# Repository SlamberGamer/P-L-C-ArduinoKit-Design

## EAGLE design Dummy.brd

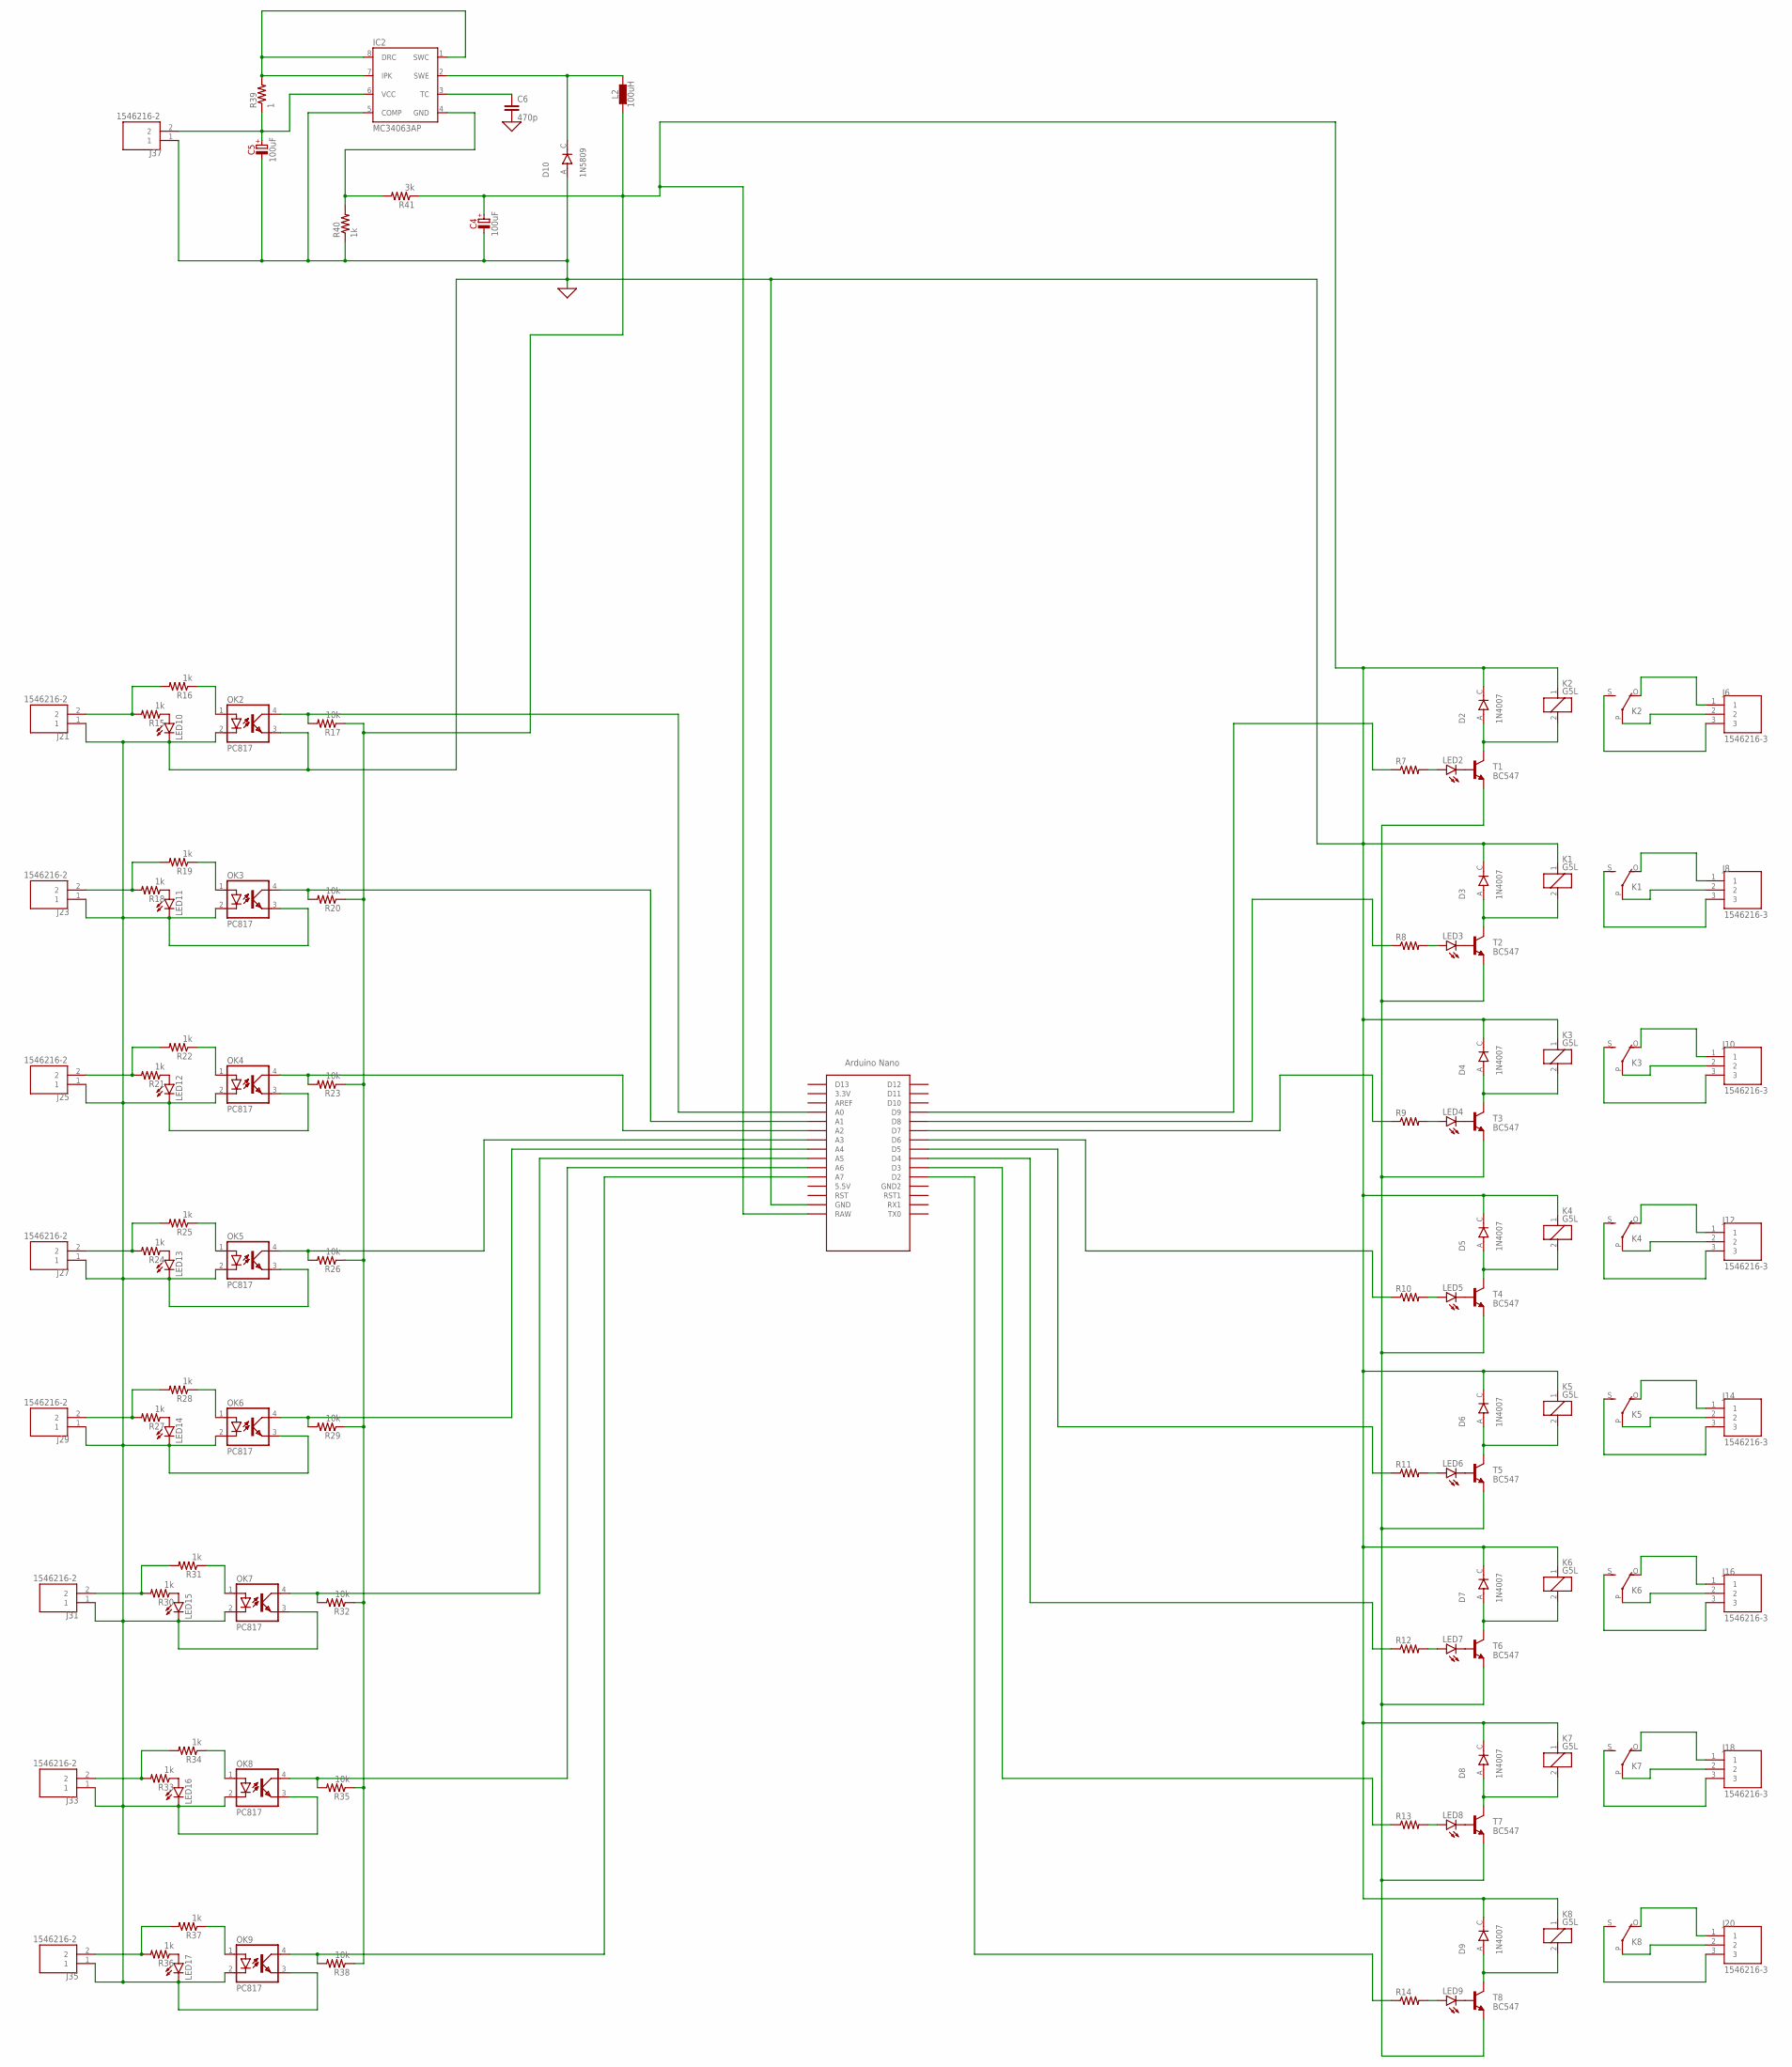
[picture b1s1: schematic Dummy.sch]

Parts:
C4, C5: 100uF; E1,5-4
C6: 470p; C2.5-2
D2, D3, D4, D5, D6, D7, D8, D9: 1N4007; DIOAD1060W80L520D270
D10: 1N5809; DIOAD1060W80L520D270
IC2: MC34063AP; DIL-08
J6, J8, J10, J12, J14, J16, J18, J20: 1546216-3; TE_1546216-3
J21, J23, J25, J27, J29, J31, J33, J35, J37: 1546216-2; TE_1546216-2
K1, K2, K3, K4, K5, K6, K7, K8: G5L; G5LE
L2: 100uH; L_NR80XX
LED2, LED3, LED4, LED5, LED6, LED7, LED8, LED9, LED10, LED11, LED12, LED13, LED14, LED15, LED16, LED17: LED3MM
OK2, OK3, OK4, OK5, OK6, OK7, OK8, OK9: PC817; DIL04
R7, R8, R9, R10, R11, R12, R13, R14: R-US_0207/15; 0207/15
R15, R16, R18, R19, R21, R22, R24, R25, R27, R28, R30, R31, R33, R34, R36, R37: 1k; 0207/15
R17, R20, R23, R26, R29, R32, R35, R38: 10k; 0207/15
R39: 1; 0207/12
R40: 1k; 0207/12
R41: 3k; 0207/12
T1, T2, T3, T4, T5, T6, T7, T8: BC547; TO92
U$1: NANO

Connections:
0: C4.+, C4.-, C5.-, C6.2, D2.C, D3.C, D4.C, D5.C, D6.C, D7.C, D8.C, D9.C, D10.A, IC2.5 (COMP), J21.1, J23.1, J25.1, J27.1, J29.1, J31.1, J33.1, J35.1, J37.1, K1.1, K2.1, K3.1, K4.1, K5.1, K6.1, K7.1, K8.1, L2.1, LED10.K (C), LED11.K (C), LED12.K (C), LED13.K (C), LED14.K (C), LED15.K (C), LED16.K (C), LED17.K (C), OK2.2 (C), OK2.3 (EMIT), OK3.2 (C), OK3.3 (EMIT), OK4.2 (C), OK4.3 (EMIT), OK5.2 (C), OK5.3 (EMIT), OK6.2 (C), OK6.3 (EMIT), OK7.2 (C), OK7.3 (EMIT), OK8.2 (C), OK8.3 (EMIT), OK9.2 (C), OK9.3 (EMIT), R17.1, R20.1, R23.1, R26.1, R29.1, R32.1, R35.1, R38.1, R40.1, R41.1, U$1.GND, U$1.RAW
unnamed: LED2.K (C), T1.2 (B)
unnamed: R7.1, U$1.D9
unnamed: LED2.A, R7.2
unnamed: D2.A, K2.2, T1.3 (C)
unnamed: J6.1, K2.O
unnamed: J6.2, K2.P
unnamed: J6.3, K2.S
unnamed: LED3.K (C), T2.2 (B)
unnamed: R8.1, U$1.D8
unnamed: LED3.A, R8.2
unnamed: D3.A, K1.2, T2.3 (C)
unnamed: J8.1, K1.O
unnamed: J8.2, K1.P
unnamed: J8.3, K1.S
unnamed: LED4.K (C), T3.2 (B)
unnamed: R9.1, U$1.D7
unnamed: LED4.A, R9.2
unnamed: D4.A, K3.2, T3.3 (C)
unnamed: J10.1, K3.O
unnamed: J10.2, K3.P
unnamed: J10.3, K3.S
unnamed: LED5.K (C), T4.2 (B)
unnamed: R10.1, U$1.D6
unnamed: LED5.A, R10.2
unnamed: D5.A, K4.2, T4.3 (C)
unnamed: J12.1, K4.O
unnamed: J12.2, K4.P
unnamed: J12.3, K4.S
unnamed: LED6.K (C), T5.2 (B)
unnamed: R11.1, U$1.D5
unnamed: LED6.A, R11.2
unnamed: D6.A, K5.2, T5.3 (C)
unnamed: J14.1, K5.O
unnamed: J14.2, K5.P
unnamed: J14.3, K5.S
unnamed: LED7.K (C), T6.2 (B)
unnamed: R12.1, U$1.D4
unnamed: LED7.A, R12.2
unnamed: D7.A, K6.2, T6.3 (C)
unnamed: J16.1, K6.O
unnamed: J16.2, K6.P
unnamed: J16.3, K6.S
unnamed: LED8.K (C), T7.2 (B)
unnamed: R13.1, U$1.D3
unnamed: LED8.A, R13.2
unnamed: D8.A, K7.2, T7.3 (C)
unnamed: J18.1, K7.O
unnamed: J18.2, K7.P
unnamed: J18.3, K7.S
unnamed: LED9.K (C), T8.2 (B)
unnamed: R14.1, U$1.D2
unnamed: LED9.A, R14.2
unnamed: D9.A, K8.2, T8.3 (C)
unnamed: T1.1 (E), T2.1 (E), T3.1 (E), T4.1 (E), T5.1 (E), T6.1 (E), T7.1 (E), T8.1 (E)
unnamed: J20.1, K8.O
unnamed: J20.2, K8.P
unnamed: J20.3, K8.S
unnamed: LED10.A, R15.1
unnamed: J21.2, R15.2, R16.2
unnamed: OK2.1 (A), R16.1
unnamed: OK2.4 (COL), R17.2, U$1.A0
unnamed: LED11.A, R18.1
unnamed: J23.2, R18.2, R19.2
unnamed: OK3.1 (A), R19.1
unnamed: OK3.4 (COL), R20.2, U$1.A1
unnamed: LED12.A, R21.1
unnamed: J25.2, R21.2, R22.2
unnamed: OK4.1 (A), R22.1
unnamed: OK4.4 (COL), R23.2, U$1.A2
unnamed: LED13.A, R24.1
unnamed: J27.2, R24.2, R25.2
unnamed: OK5.1 (A), R25.1
unnamed: OK5.4 (COL), R26.2, U$1.A3
unnamed: LED14.A, R27.1
unnamed: J29.2, R27.2, R28.2
unnamed: OK6.1 (A), R28.1
unnamed: OK6.4 (COL), R29.2, U$1.A4
unnamed: LED15.A, R30.1
unnamed: J31.2, R30.2, R31.2
unnamed: OK7.1 (A), R31.1
unnamed: OK7.4 (COL), R32.2, U$1.A5
unnamed: LED16.A, R33.1
unnamed: J33.2, R33.2, R34.2
unnamed: OK8.1 (A), R34.1
unnamed: OK8.4 (COL), R35.2, U$1.A6
unnamed: LED17.A, R36.1
unnamed: J35.2, R36.2, R37.2
unnamed: OK9.1 (A), R37.1
unnamed: OK9.4 (COL), R38.2, U$1.A7
unnamed: IC2.1 (SWC), IC2.7 (IPK), IC2.8 (DRC), R39.2
unnamed: D10.C, IC2.2 (SWE), L2.2
unnamed: C6.1, IC2.3 (TC)
unnamed: IC2.4 (GND), R40.2, R41.2
unnamed: C5.+, IC2.6 (VCC), J37.2, R39.1

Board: 2 copper layers, 107 parts (0 on the bottom side), 95 nets, no tracks yet.

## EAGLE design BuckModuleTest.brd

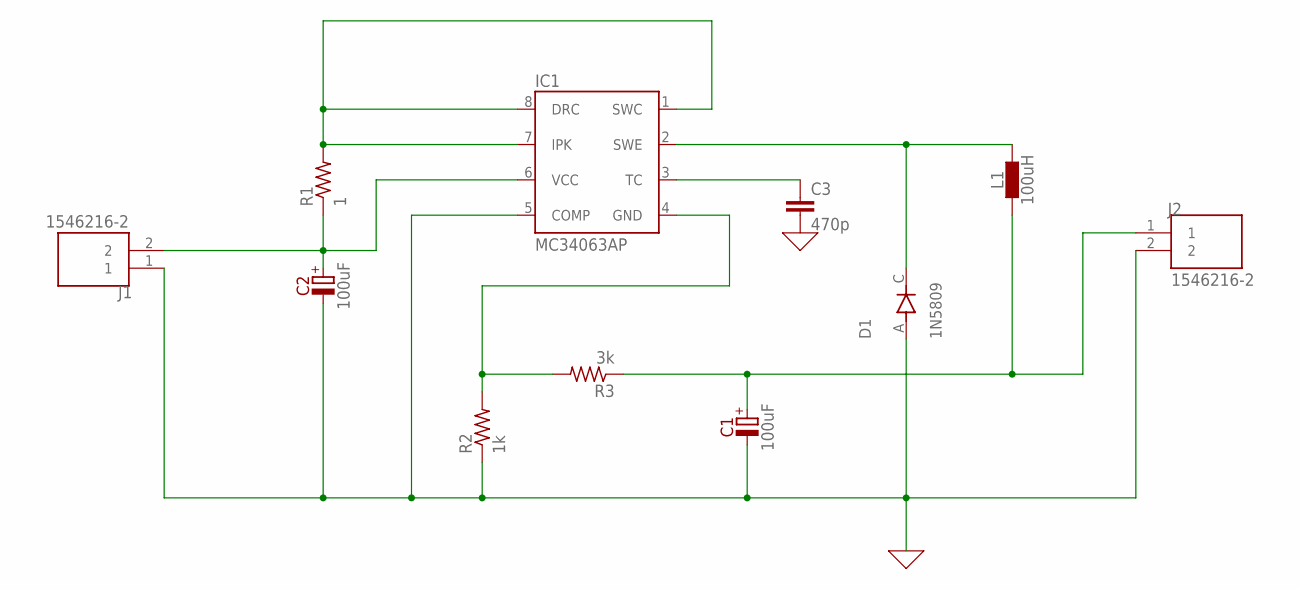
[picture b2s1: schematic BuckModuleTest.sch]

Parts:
C1, C2: 100uF; E1,5-4
C3: 470p; C2.5-2
D1: 1N5809; DIOAD1060W80L520D270
IC1: MC34063AP; DIL-08
J1, J2: 1546216-2; TE_1546216-2
L1: 100uH; L_NR80XX
R1: 1; 0207/12
R2: 1k; 0207/12
R3: 3k; 0207/12

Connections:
0: C1.-, C2.-, C3.2, D1.A, IC1.5 (COMP), J1.1, J2.2, R2.1
unnamed: IC1.1 (SWC), IC1.7 (IPK), IC1.8 (DRC), R1.2
unnamed: D1.C, IC1.2 (SWE), L1.2
unnamed: C3.1, IC1.3 (TC)
unnamed: IC1.4 (GND), R2.2, R3.2
unnamed: C1.+, J2.1, L1.1, R3.1
unnamed: C2.+, IC1.6 (VCC), J1.2, R1.1

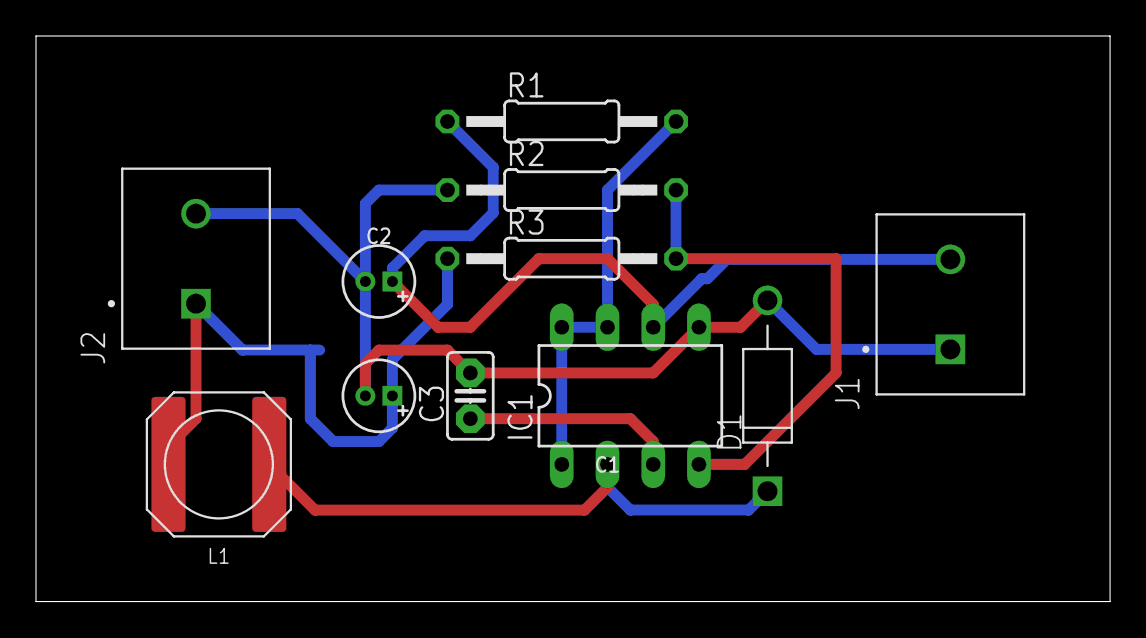
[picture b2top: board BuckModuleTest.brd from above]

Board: 2 copper layers, 59.7 x 31.4 mm, 11 parts (0 on the bottom side), 7 nets.

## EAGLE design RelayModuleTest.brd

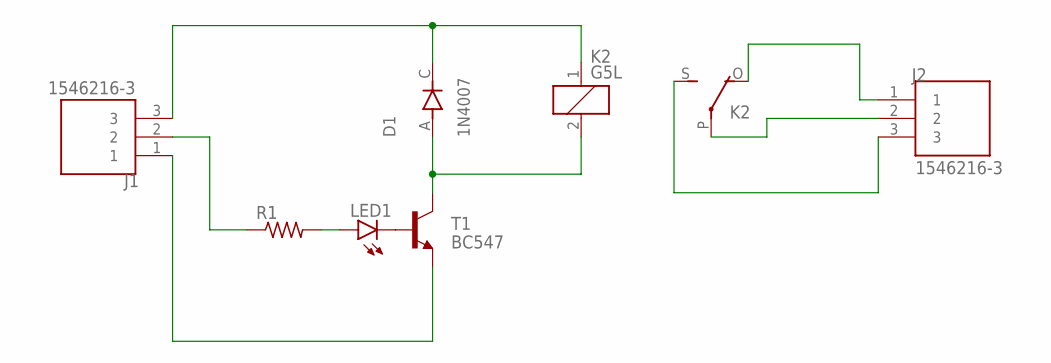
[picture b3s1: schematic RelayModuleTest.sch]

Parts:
D1: 1N4007; DIOAD1060W80L520D270
J1, J2: 1546216-3; TE_1546216-3
K2: G5L; G5LE
LED1: LED3MM
R1: R-US_0207/15; 0207/15
T1: BC547; TO92

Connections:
unnamed: LED1.K (C), T1.2 (B)
unnamed: J1.2, R1.1
unnamed: LED1.A, R1.2
unnamed: D1.A, K2.2, T1.3 (C)
unnamed: J1.1, T1.1 (E)
unnamed: D1.C, J1.3, K2.1
unnamed: J2.1, K2.O
unnamed: J2.2, K2.P
unnamed: J2.3, K2.S

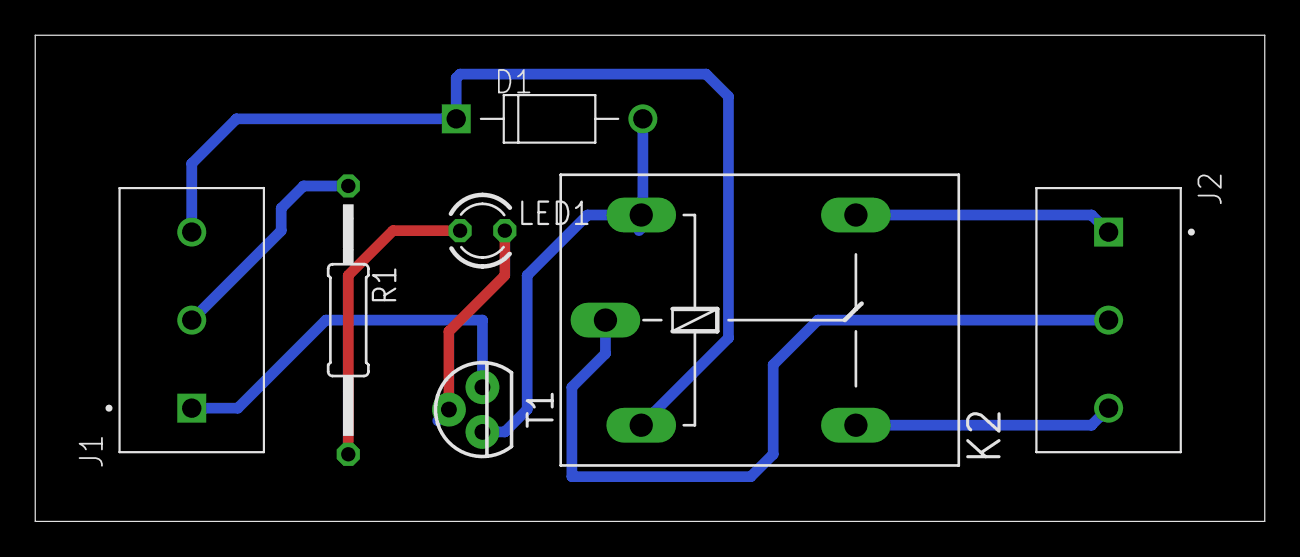
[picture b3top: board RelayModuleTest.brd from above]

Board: 2 copper layers, 69.8 x 27.6 mm, 7 parts (0 on the bottom side), 9 nets.

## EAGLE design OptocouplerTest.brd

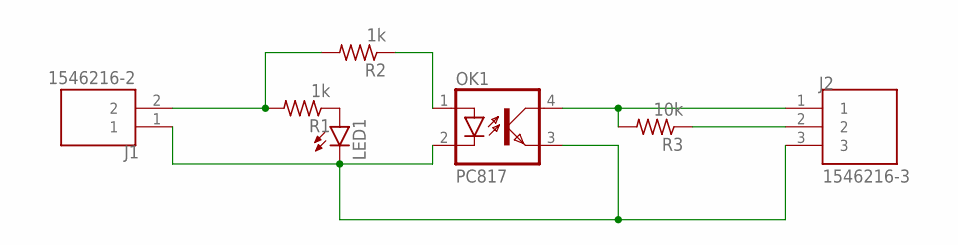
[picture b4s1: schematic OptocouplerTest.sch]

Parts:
J1: 1546216-2; TE_1546216-2
J2: 1546216-3; TE_1546216-3
LED1: LED3MM
OK1: PC817; DIL04
R1, R2: 1k; 0207/15
R3: 10k; 0207/15

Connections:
unnamed: LED1.A, R1.1
unnamed: J1.2, R1.2, R2.2
unnamed: OK1.1 (A), R2.1
unnamed: J1.1, J2.3, LED1.K (C), OK1.2 (C), OK1.3 (EMIT)
unnamed: J2.2, R3.1
unnamed: J2.1, OK1.4 (COL), R3.2

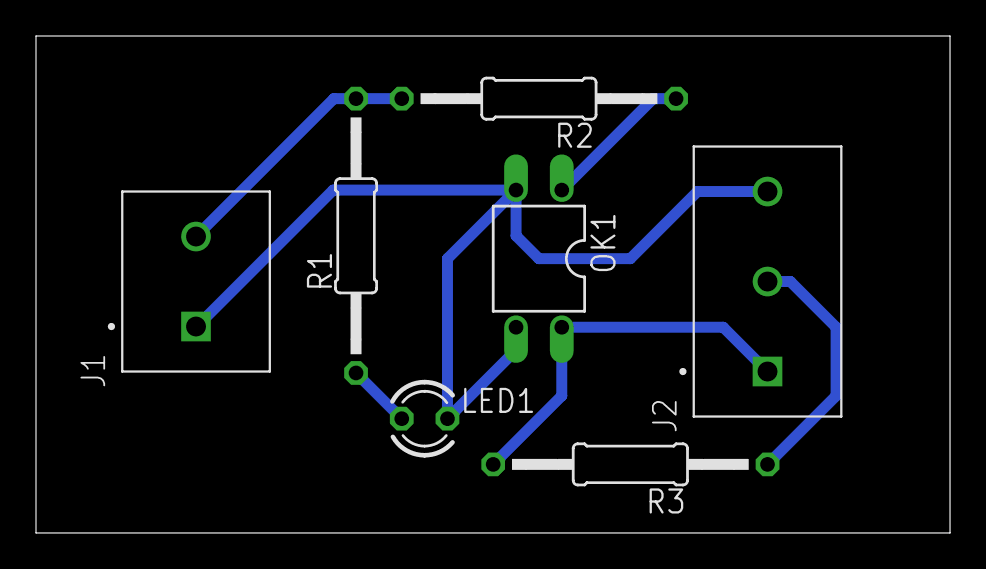
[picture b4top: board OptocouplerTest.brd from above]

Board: 2 copper layers, 50.8 x 27.6 mm, 7 parts (0 on the bottom side), 6 nets.

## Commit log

2022-11-10 update lastest working design
    working :)
